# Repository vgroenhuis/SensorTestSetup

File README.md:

# SensorTestSetup

A permanent desk setup of common lab sensors and actuators around one ESP32-C5, used to explain and try out each part.
Switch it on and everything works: every part has a live page in the browser, on the university network or through the
CloSer lab demos site (https://closer.ram.eemcs.utwente.nl/labdemos/demo?id=sensortest).

| Folder | What |
| --- | --- |
| [`firmware/`](firmware/) | The firmware (ESP-IDF 6.1): every part, its web pages, the input-output matrix, updates over the air |
| [`labdemo/`](labdemo/) | The lab demos page for it (`demo.json`, `README.md`): copied to the server |
| [`ESP32_C5_Breadboard_PlatformIO/`](ESP32_C5_Breadboard_PlatformIO/) | The earlier Arduino/PlatformIO firmware, kept for reference (its README pinout is older than the wiring: `firmware/main/board.h` has the pins) |
| [`Electronics_KiCad/`](Electronics_KiCad/) | KiCad files of the setup |

The parts: SSD1306 OLED, MCP3008 (potentiometer, MH sensor), MCP23017, PCA9685 servos, TCA9548 with two WF100DPZ pressure
sensors, VL53L7CX time-of-flight, HC-SR04 ultrasonic, HX711 load cell, L298N with a DC gear motor and encoder. Build,
first flash and updates: [`firmware/README.md`](firmware/README.md).

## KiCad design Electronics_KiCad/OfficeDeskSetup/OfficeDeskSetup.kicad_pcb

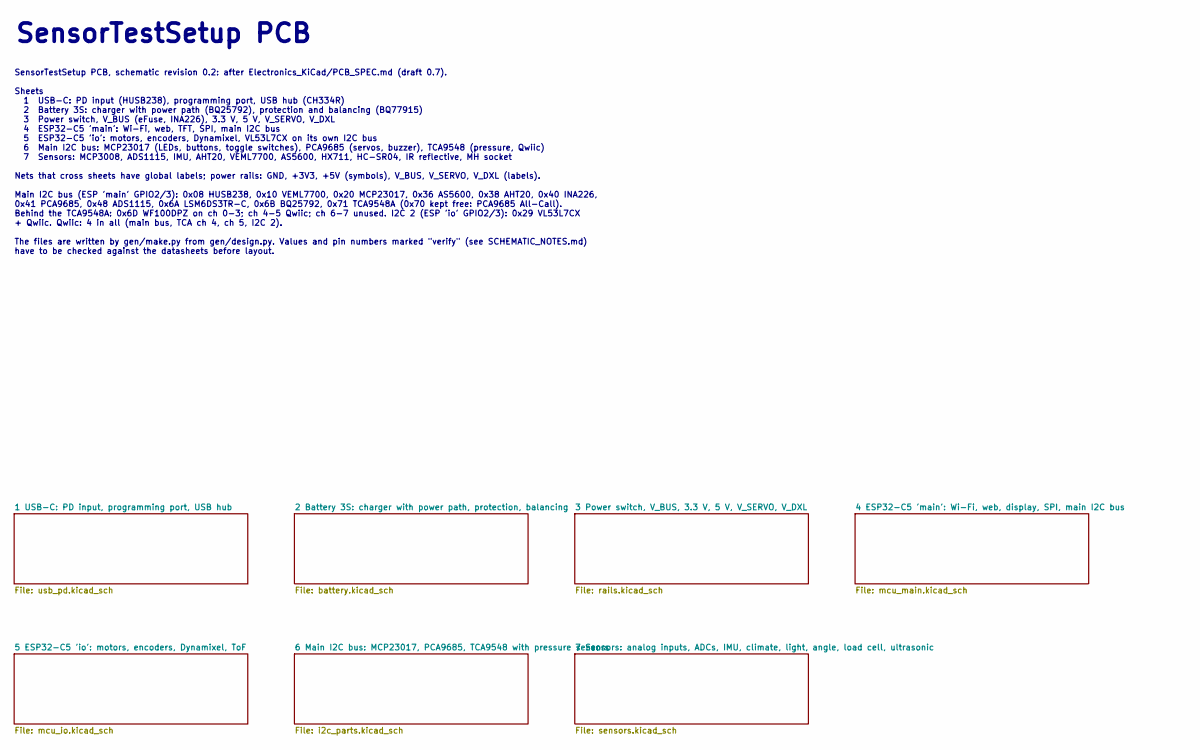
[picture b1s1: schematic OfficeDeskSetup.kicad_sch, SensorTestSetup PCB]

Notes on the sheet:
SensorTestSetup PCB
SensorTestSetup PCB, schematic revision 0.2: after Electronics_KiCad/PCB_SPEC.md (draft 0.7). Sheets 1 USB-C: PD input (HUSB238), programming port, USB hub (CH334R) 2 Battery 3S: charger with power path (BQ25792), protection and balancing (BQ77915) 3 Power switch, V_BUS (eFuse, INA226), 3.3 V, 5 V,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

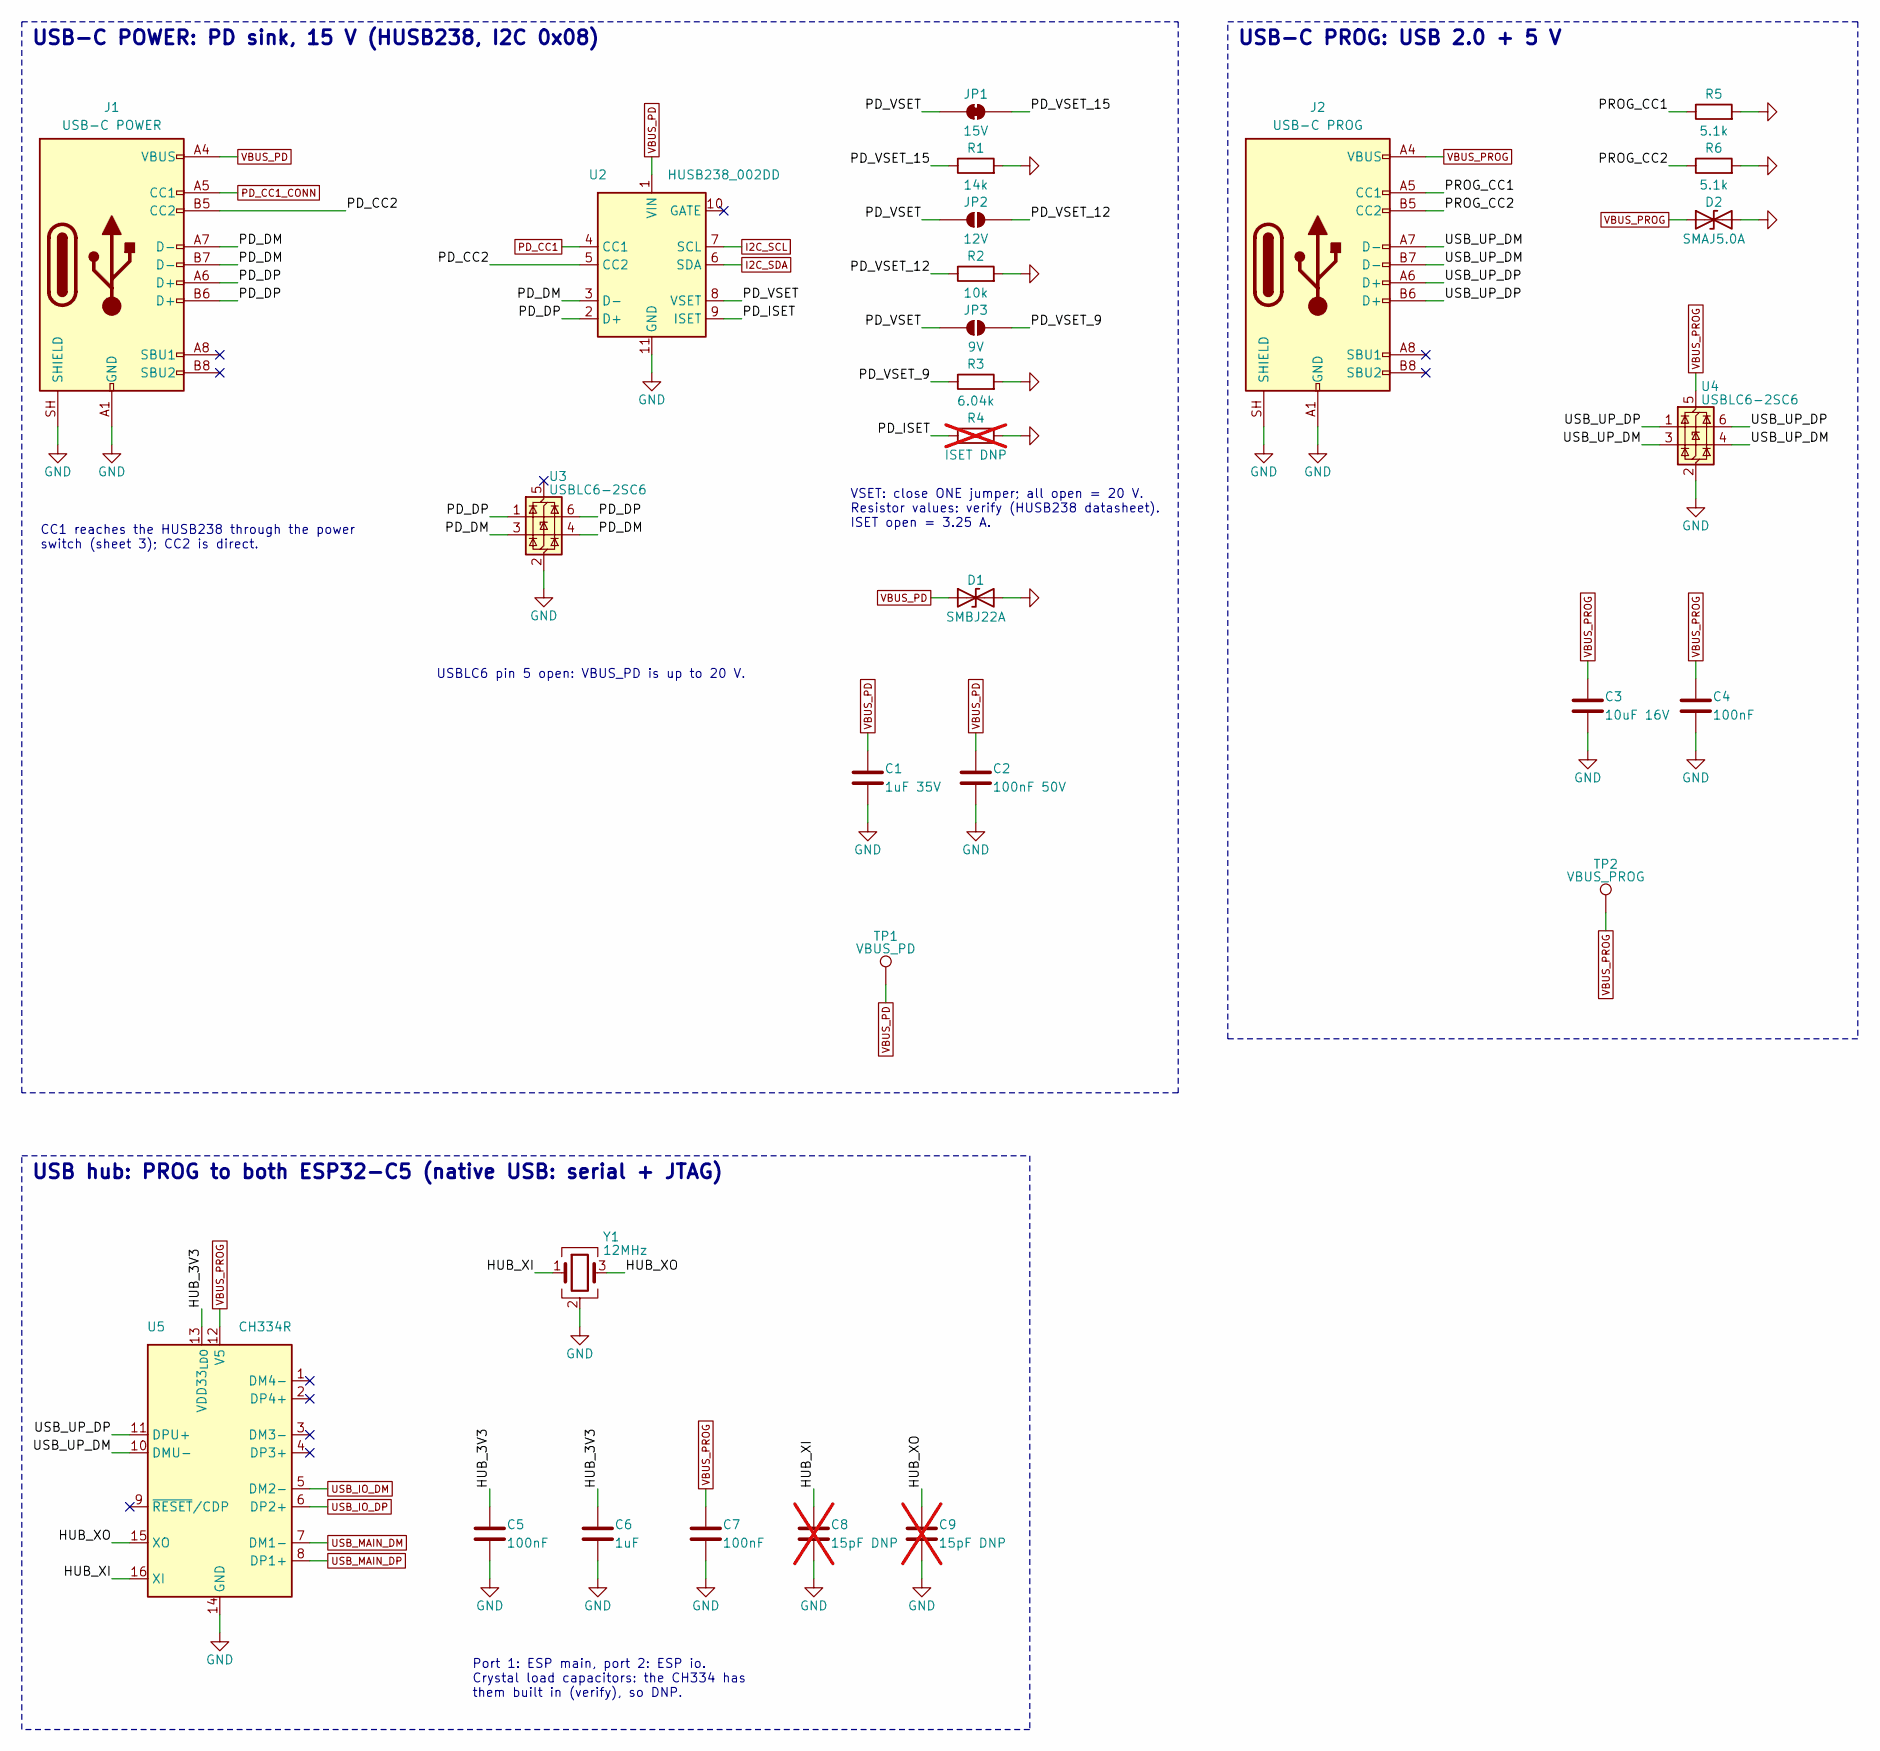
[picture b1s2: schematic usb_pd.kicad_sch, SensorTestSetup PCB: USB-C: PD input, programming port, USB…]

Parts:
C1: 1uF 35V; C_0805_2012Metric; LCSC C28323
C2: 100nF 50V; C_0603_1608Metric; LCSC C14663
C3: 10uF 16V; C_0805_2012Metric; LCSC C15850
C4, C5, C7: 100nF; C_0603_1608Metric; LCSC C14663
C6: 1uF; C_0603_1608Metric; LCSC C15849
C8, C9: 15pF DNP; C_0603_1608Metric; LCSC C1644; not fitted
D1: SMBJ22A; D_SMB; LCSC C10214
D2: SMAJ5.0A; D_SMA; LCSC C19077523
J1: USB-C POWER; USB_C_Receptacle_HRO_TYPE-C-31-M-12; LCSC C165948
J2: USB-C PROG; USB_C_Receptacle_HRO_TYPE-C-31-M-12; LCSC C165948
JP1: 15V; SolderJumper-2_P1.3mm_Bridged_RoundedPad1.0x1.5mm
JP2: 12V; SolderJumper-2_P1.3mm_Open_RoundedPad1.0x1.5mm
JP3: 9V; SolderJumper-2_P1.3mm_Open_RoundedPad1.0x1.5mm
R1: 14k; R_0603_1608Metric; LCSC C22803
R2: 10k; R_0603_1608Metric; LCSC C25804
R3: 6.04k; R_0603_1608Metric; LCSC C25977
R4: ISET DNP; R_0603_1608Metric; not fitted
R5, R6: 5.1k; R_0603_1608Metric; LCSC C23186
TP1: VBUS_PD; TestPoint_Pad_D1.5mm
TP2: VBUS_PROG; TestPoint_Pad_D1.5mm
U2: HUSB238_002DD; WDFN-10-1EP_3x3mm_P0.5mm_EP1.8x2.5mm; LCSC C7471904
U3, U4: USBLC6-2SC6; SOT-23-6; LCSC C2827654
U5: CH334R; QSOP-16_3.9x4.9mm_P0.635mm; LCSC C4154405
Y1: 12MHz; Crystal_SMD_3225-4Pin_3.2x2.5mm; LCSC C9002

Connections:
/1 USB-C: PD input, programming port, USB hub/HUB_3V3: C5.1, C6.1, U5.13 (VDD33_{LDO})
/1 USB-C: PD input, programming port, USB hub/HUB_XI: C8.1, U5.16 (XI), Y1.1
/1 USB-C: PD input, programming port, USB hub/HUB_XO: C9.1, U5.15 (XO), Y1.3
/1 USB-C: PD input, programming port, USB hub/PD_CC2: J1.B5 (CC2), U2.5 (CC2)
/1 USB-C: PD input, programming port, USB hub/PD_DM: J1.A7 (D-), J1.B7 (D-), U2.3 (D-), U3.3 (I/O2), U3.4 (I/O2)
/1 USB-C: PD input, programming port, USB hub/PD_DP: J1.A6 (D+), J1.B6 (D+), U2.2 (D+), U3.1 (I/O1), U3.6 (I/O1)
/1 USB-C: PD input, programming port, USB hub/PD_ISET: R4.1, U2.9 (ISET)
/1 USB-C: PD input, programming port, USB hub/PD_VSET: JP1.1 (A), JP2.1 (A), JP3.1 (A), U2.8 (VSET)
/1 USB-C: PD input, programming port, USB hub/PD_VSET_9: JP3.2 (B), R3.1
/1 USB-C: PD input, programming port, USB hub/PD_VSET_12: JP2.2 (B), R2.1
/1 USB-C: PD input, programming port, USB hub/PD_VSET_15: JP1.2 (B), R1.1
/1 USB-C: PD input, programming port, USB hub/PROG_CC1: J2.A5 (CC1), R5.1
/1 USB-C: PD input, programming port, USB hub/PROG_CC2: J2.B5 (CC2), R6.1
/1 USB-C: PD input, programming port, USB hub/USB_UP_DM: J2.A7 (D-), J2.B7 (D-), U4.3 (I/O2), U4.4 (I/O2), U5.10 (DMU-)
/1 USB-C: PD input, programming port, USB hub/USB_UP_DP: J2.A6 (D+), J2.B6 (D+), U4.1 (I/O1), U4.6 (I/O1), U5.11 (DPU+)
GND: C1.2, C2.2, C3.2, C4.2, C5.2, C6.2, C7.2, C8.2, C9.2, D1.2 (A2), D2.2 (A2), J1.A1 (GND), J1.A12 (GND), J1.B1 (GND), J1.B12 (GND), J1.SH (SHIELD), J2.A1 (GND), J2.A12 (GND), J2.B1 (GND), J2.B12 (GND), J2.SH (SHIELD), R1.2, R2.2, R3.2, R4.2, R5.2, R6.2, U2.11 (GND), U3.2 (GND), U4.2 (GND), U5.14 (GND), Y1.2 (G), Y1.4 (G); also elsewhere on the board
I2C_SCL: U2.7 (SCL); also elsewhere on the board
I2C_SDA: U2.6 (SDA); also elsewhere on the board
PD_CC1: U2.4 (CC1); also elsewhere on the board
PD_CC1_CONN: J1.A5 (CC1); also elsewhere on the board
USB_IO_DM: U5.5 (DM2-); also elsewhere on the board
USB_IO_DP: U5.6 (DP2+); also elsewhere on the board
USB_MAIN_DM: U5.7 (DM1-); also elsewhere on the board
USB_MAIN_DP: U5.8 (DP1+); also elsewhere on the board
VBUS_PD: C1.1, C2.1, D1.1 (A1), J1.A4 (VBUS), J1.A9 (VBUS), J1.B4 (VBUS), J1.B9 (VBUS), TP1.1, U2.1 (VIN); also elsewhere on the board
VBUS_PROG: C3.1, C4.1, C7.1, D2.1 (A1), J2.A4 (VBUS), J2.A9 (VBUS), J2.B4 (VBUS), J2.B9 (VBUS), TP2.1, U4.5 (VBUS), U5.12 (V5); also elsewhere on the board

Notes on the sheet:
CC1 reaches the HUSB238 through the power switch (sheet 3); CC2 is direct.
USBLC6 pin 5 open: VBUS_PD is up to 20 V.
VSET: close ONE jumper; all open = 20 V. Resistor values: verify (HUSB238 datasheet). ISET open = 3.25 A.
USB-C POWER: PD sink, 15 V (HUSB238, I2C 0x08)
USB-C PROG: USB 2.0 + 5 V
Port 1: ESP main, port 2: ESP io. Crystal load capacitors: the CH334 has them built in (verify), so DNP.
USB hub: PROG to both ESP32-C5 (native USB: serial + JTAG)

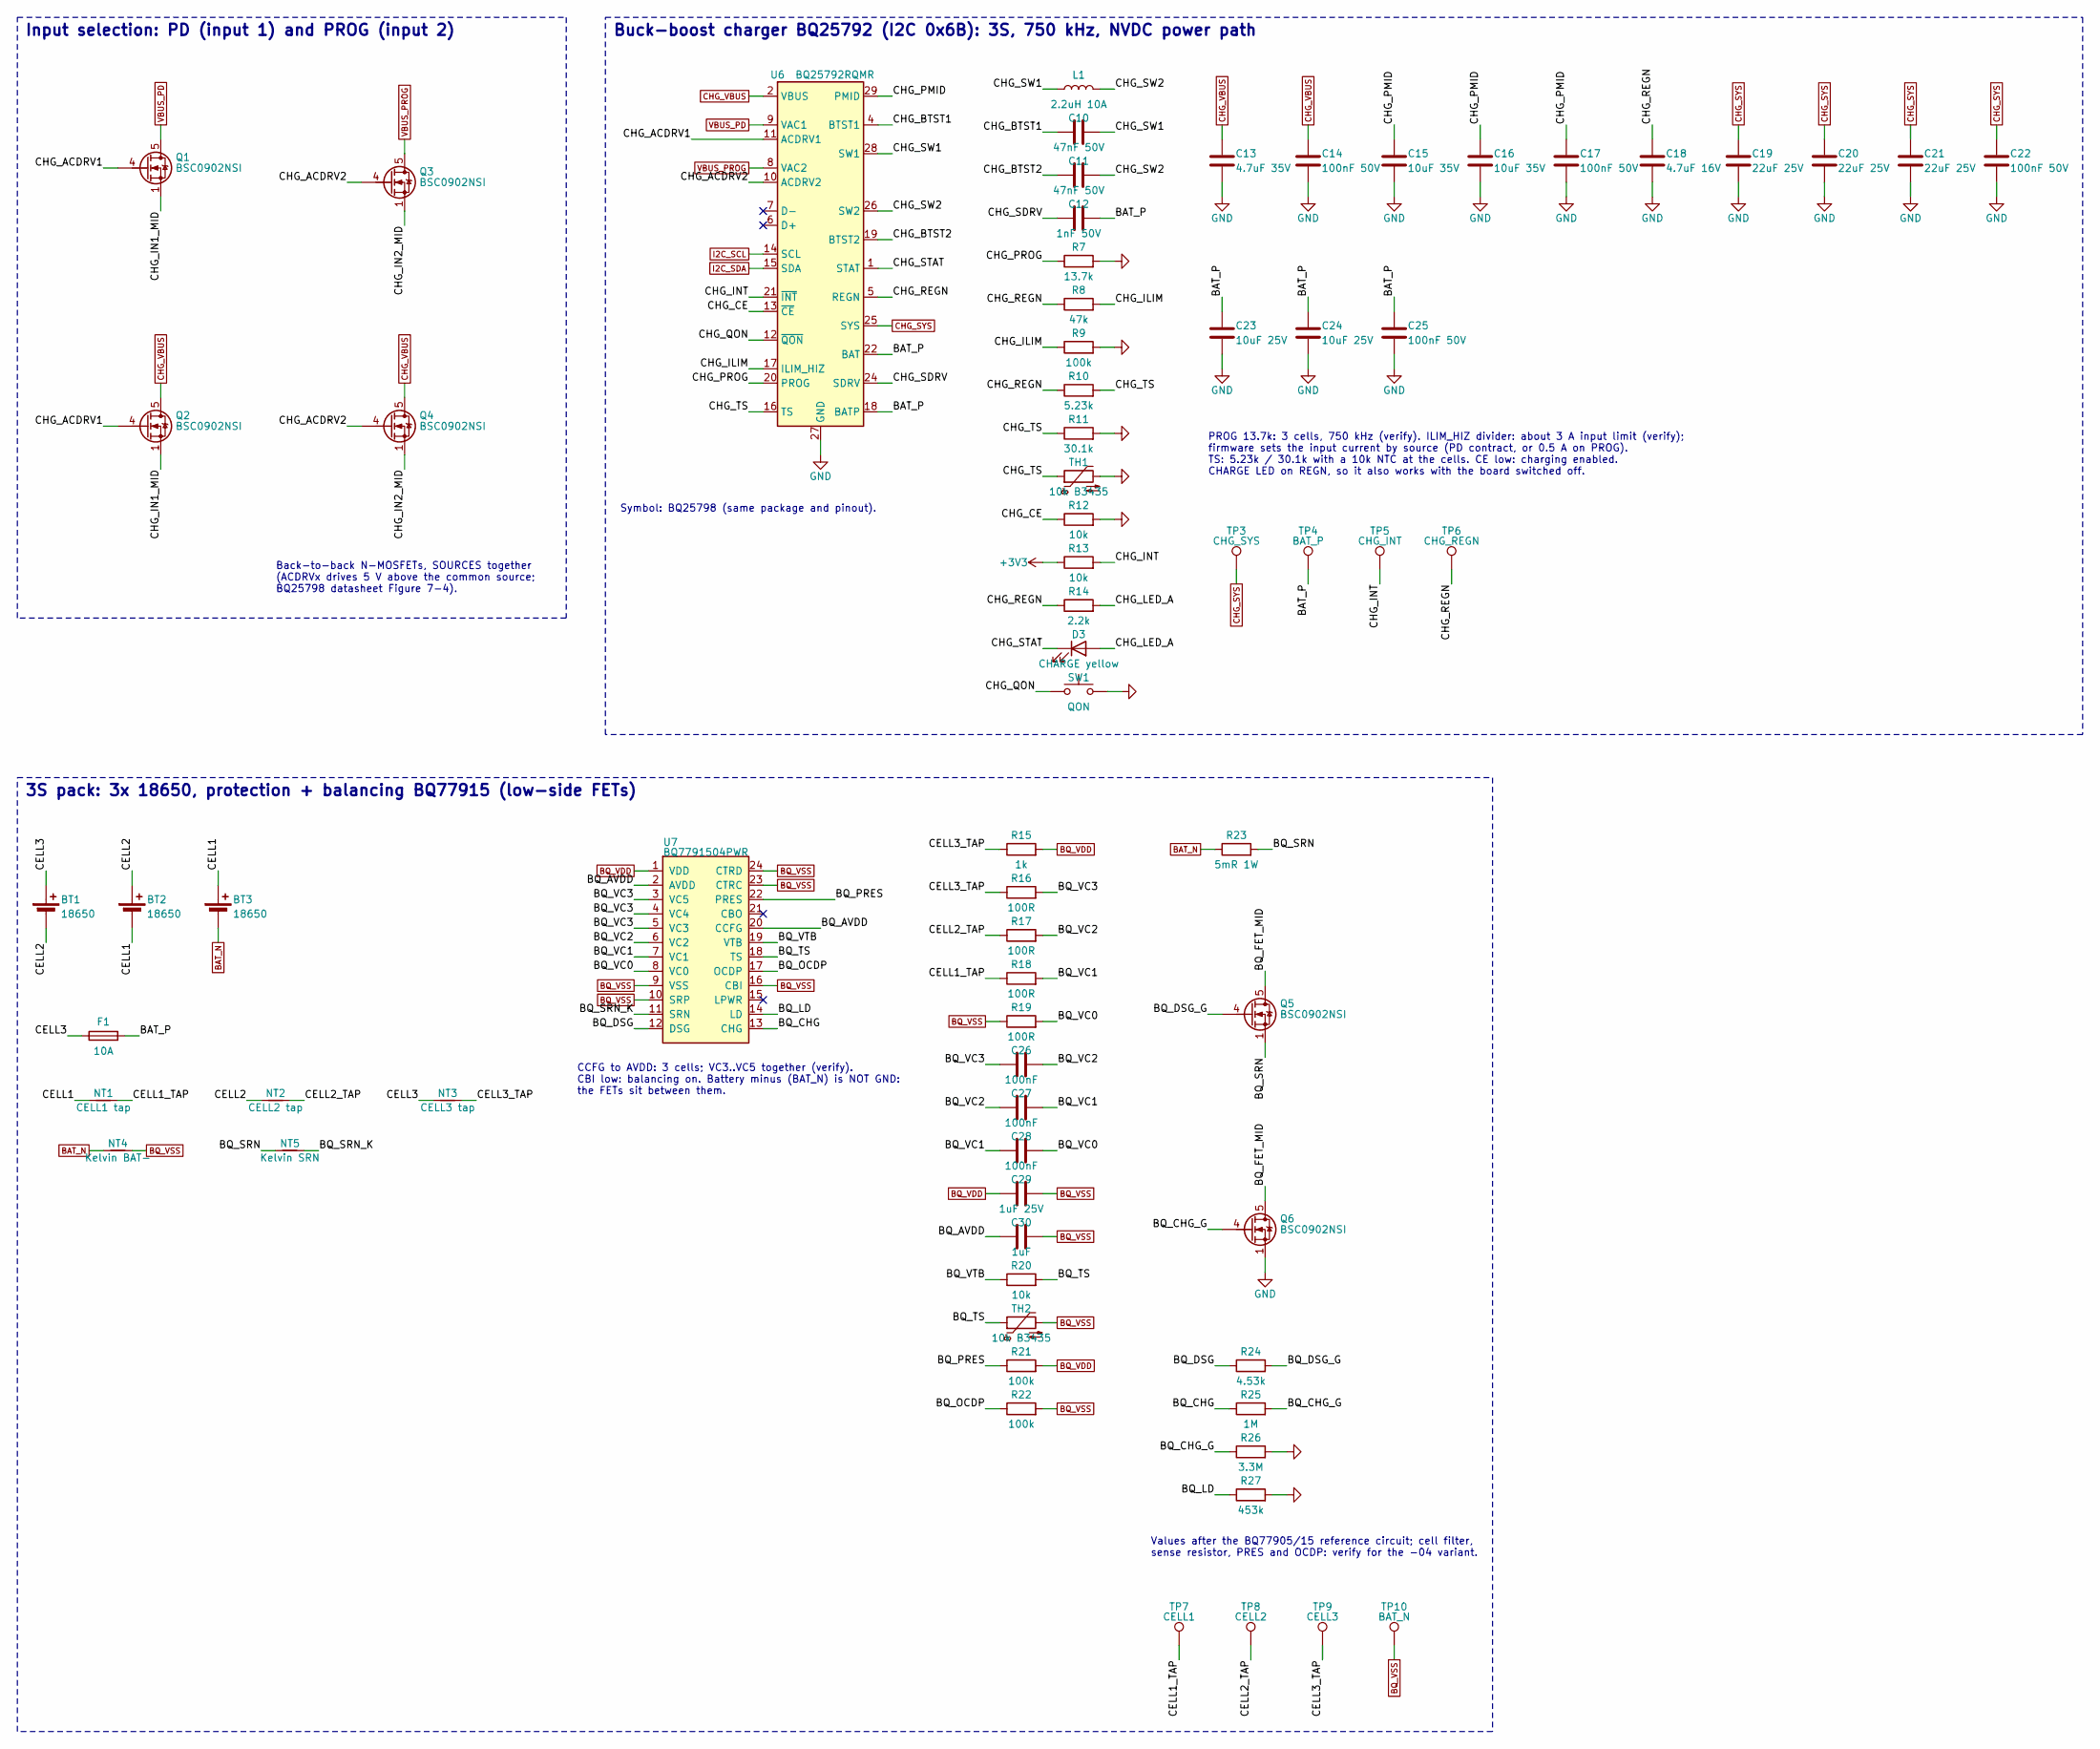
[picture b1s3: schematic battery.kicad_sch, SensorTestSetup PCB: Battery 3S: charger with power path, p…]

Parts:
BT1, BT2, BT3: 18650; BatteryHolder_Keystone_1042_1x18650; LCSC C2979183
C10, C11: 47nF 50V; C_0603_1608Metric; LCSC C1622
C12: 1nF 50V; C_0603_1608Metric; LCSC C1588
C13: 4.7uF 35V; C_0805_2012Metric; LCSC C76651
C14, C17, C22, C25: 100nF 50V; C_0603_1608Metric; LCSC C14663
C15, C16: 10uF 35V; C_1206_3216Metric; LCSC C13585
C18: 4.7uF 16V; C_0805_2012Metric; LCSC C1779
C19, C20, C21: 22uF 25V; C_1206_3216Metric; LCSC C12891
C23, C24: 10uF 25V; C_1206_3216Metric; LCSC C13585
C26, C27, C28: 100nF; C_0603_1608Metric; LCSC C14663
C29: 1uF 25V; C_0603_1608Metric; LCSC C15849
C30: 1uF; C_0603_1608Metric; LCSC C15849
D3: CHARGE yellow; LED_0603_1608Metric; LCSC C2287
F1: 10A; Fuse_Littelfuse-NANO2-451_453; LCSC C44479
L1: 2.2uH 10A; IND-SMD_L11.5-W10.5; LCSC C167228
NT1: CELL1 tap; NetTie-2_SMD_Pad0.5mm
NT2: CELL2 tap; NetTie-2_SMD_Pad0.5mm
NT3: CELL3 tap; NetTie-2_SMD_Pad0.5mm
NT4: Kelvin BAT-; NetTie-2_SMD_Pad0.5mm
NT5: Kelvin SRN; NetTie-2_SMD_Pad0.5mm
Q1, Q2, Q3, Q4, Q5, Q6: BSC0902NSI; TDSON-8-1; LCSC C534382
R7: 13.7k; R_0603_1608Metric; LCSC C22793
R8: 47k; R_0603_1608Metric; LCSC C25819
R9, R21, R22: 100k; R_0603_1608Metric; LCSC C25803
R10: 5.23k; R_0603_1608Metric; LCSC C23068
R11: 30.1k; R_0603_1608Metric; LCSC C23000
R12, R13, R20: 10k; R_0603_1608Metric; LCSC C25804
R14: 2.2k; R_0603_1608Metric; LCSC C4190
R15: 1k; R_0603_1608Metric; LCSC C21190
R16, R17, R18, R19: 100R; R_0603_1608Metric; LCSC C22775
R23: 5mR 1W; R_2512_6332Metric; LCSC C393074
R24: 4.53k; R_0603_1608Metric; LCSC C25971
R25: 1M; R_0603_1608Metric; LCSC C22935
R26: 3.3M; R_0603_1608Metric; LCSC C26096
R27: 453k; R_0603_1608Metric; LCSC C25818
SW1: QON; SW-SMD_4P-L5.1-W5.1-P3.70-LS6.5-TL_H1.5; LCSC C318884
TH1, TH2: 10k B3435; R_0603_1608Metric; LCSC C525660
TP3: CHG_SYS; TestPoint_Pad_D1.5mm
TP4: BAT_P; TestPoint_Pad_D1.5mm
TP5: CHG_INT; TestPoint_Pad_D1.5mm
TP6: CHG_REGN; TestPoint_Pad_D1.5mm
TP7: CELL1; TestPoint_Pad_D1.5mm
TP8: CELL2; TestPoint_Pad_D1.5mm
TP9: CELL3; TestPoint_Pad_D1.5mm
TP10: BAT_N; TestPoint_Pad_D1.5mm
U6: BQ25792RQMR; Texas_RQM0029A_VQFN-29_4x4mm_P0.4mm; LCSC C2862876
U7: BQ7791504PWR; TSSOP-24_4.4x7.8mm_P0.65mm; LCSC C2873309

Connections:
+3V3: R13.1; also elsewhere on the board
/2 Battery 3S: charger with power path, protection, balancing/BAT_P: C12.2, C23.1, C24.1, C25.1, F1.2, TP4.1, U6.18 (BATP), U6.22 (BAT), U6.23 (BAT)
/2 Battery 3S: charger with power path, protection, balancing/BQ_AVDD: C30.1, U7.2 (AVDD), U7.20 (CCFG)
/2 Battery 3S: charger with power path, protection, balancing/BQ_CHG: R25.1, U7.13 (CHG)
/2 Battery 3S: charger with power path, protection, balancing/BQ_CHG_G: Q6.4 (G), R25.2, R26.1
/2 Battery 3S: charger with power path, protection, balancing/BQ_DSG: R24.1, U7.12 (DSG)
/2 Battery 3S: charger with power path, protection, balancing/BQ_DSG_G: Q5.4 (G), R24.2
/2 Battery 3S: charger with power path, protection, balancing/BQ_FET_MID: Q5.5 (D), Q6.5 (D)
/2 Battery 3S: charger with power path, protection, balancing/BQ_LD: R27.1, U7.14 (LD)
/2 Battery 3S: charger with power path, protection, balancing/BQ_OCDP: R22.1, U7.17 (OCDP)
/2 Battery 3S: charger with power path, protection, balancing/BQ_PRES: R21.1, U7.22 (PRES)
/2 Battery 3S: charger with power path, protection, balancing/BQ_SRN: NT5.1, Q5.1 (S), Q5.2 (S), Q5.3 (S), R23.2
/2 Battery 3S: charger with power path, protection, balancing/BQ_SRN_K: NT5.2, U7.11 (SRN)
/2 Battery 3S: charger with power path, protection, balancing/BQ_TS: R20.2, TH2.1, U7.18 (TS)
/2 Battery 3S: charger with power path, protection, balancing/BQ_VC0: C28.2, R19.2, U7.8 (VC0)
/2 Battery 3S: charger with power path, protection, balancing/BQ_VC1: C27.2, C28.1, R18.2, U7.7 (VC1)
/2 Battery 3S: charger with power path, protection, balancing/BQ_VC2: C26.2, C27.1, R17.2, U7.6 (VC2)
/2 Battery 3S: charger with power path, protection, balancing/BQ_VC3: C26.1, R16.2, U7.3 (VC5), U7.4 (VC4), U7.5 (VC3)
/2 Battery 3S: charger with power path, protection, balancing/BQ_VTB: R20.1, U7.19 (VTB)
/2 Battery 3S: charger with power path, protection, balancing/CELL1: BT2.2 (-), BT3.1 (+), NT1.1
/2 Battery 3S: charger with power path, protection, balancing/CELL1_TAP: NT1.2, R18.1, TP7.1
/2 Battery 3S: charger with power path, protection, balancing/CELL2: BT1.2 (-), BT2.1 (+), NT2.1
/2 Battery 3S: charger with power path, protection, balancing/CELL2_TAP: NT2.2, R17.1, TP8.1
/2 Battery 3S: charger with power path, protection, balancing/CELL3: BT1.1 (+), F1.1, NT3.1
/2 Battery 3S: charger with power path, protection, balancing/CELL3_TAP: NT3.2, R15.1, R16.1, TP9.1
/2 Battery 3S: charger with power path, protection, balancing/CHG_ACDRV1: Q1.4 (G), Q2.4 (G), U6.11 (ACDRV1)
/2 Battery 3S: charger with power path, protection, balancing/CHG_ACDRV2: Q3.4 (G), Q4.4 (G), U6.10 (ACDRV2)
/2 Battery 3S: charger with power path, protection, balancing/CHG_BTST1: C10.1, U6.4 (BTST1)
/2 Battery 3S: charger with power path, protection, balancing/CHG_BTST2: C11.1, U6.19 (BTST2)
/2 Battery 3S: charger with power path, protection, balancing/CHG_CE: R12.1, U6.13 (~CE)
/2 Battery 3S: charger with power path, protection, balancing/CHG_ILIM: R8.2, R9.1, U6.17 (ILIM_HIZ)
/2 Battery 3S: charger with power path, protection, balancing/CHG_IN1_MID: Q1.1 (S), Q1.2 (S), Q1.3 (S), Q2.1 (S), Q2.2 (S), Q2.3 (S)
/2 Battery 3S: charger with power path, protection, balancing/CHG_IN2_MID: Q3.1 (S), Q3.2 (S), Q3.3 (S), Q4.1 (S), Q4.2 (S), Q4.3 (S)
/2 Battery 3S: charger with power path, protection, balancing/CHG_INT: R13.2, TP5.1, U6.21 (~INT)
/2 Battery 3S: charger with power path, protection, balancing/CHG_LED_A: D3.2 (A), R14.2
/2 Battery 3S: charger with power path, protection, balancing/CHG_PMID: C15.1, C16.1, C17.1, U6.29 (PMID)
/2 Battery 3S: charger with power path, protection, balancing/CHG_PROG: R7.1, U6.20 (PROG)
/2 Battery 3S: charger with power path, protection, balancing/CHG_QON: SW1.1, U6.12 (~QON)
/2 Battery 3S: charger with power path, protection, balancing/CHG_REGN: C18.1, R8.1, R10.1, R14.1, TP6.1, U6.5 (REGN)
/2 Battery 3S: charger with power path, protection, balancing/CHG_SDRV: C12.1, U6.24 (SDRV)
/2 Battery 3S: charger with power path, protection, balancing/CHG_STAT: D3.1 (K), U6.1 (STAT)
/2 Battery 3S: charger with power path, protection, balancing/CHG_SW1: C10.2, L1.1, U6.28 (SW1)
/2 Battery 3S: charger with power path, protection, balancing/CHG_SW2: C11.2, L1.2, U6.26 (SW2)
/2 Battery 3S: charger with power path, protection, balancing/CHG_TS: R10.2, R11.1, TH1.1, U6.16 (TS)
BAT_N: BT3.2 (-), NT4.1, R23.1
BQ_VDD: C29.1, R15.2, R21.2, U7.1 (VDD)
BQ_VSS: C29.2, C30.2, NT4.2, R19.1, R22.2, TH2.2, TP10.1, U7.9 (VSS), U7.10 (SRP), U7.16 (CBI), U7.23 (CTRC), U7.24 (CTRD)
CHG_SYS: C19.1, C20.1, C21.1, C22.1, TP3.1, U6.25 (SYS); also elsewhere on the board
CHG_VBUS: C13.1, C14.1, Q2.5 (D), Q4.5 (D), U6.2 (VBUS), U6.3 (VBUS)
GND: C13.2, C14.2, C15.2, C16.2, C17.2, C18.2, C19.2, C20.2, C21.2, C22.2, C23.2, C24.2, C25.2, Q6.1 (S), Q6.2 (S), Q6.3 (S), R7.2, R9.2, R11.2, R12.2, R26.2, R27.2, SW1.2, TH1.2, U6.27 (GND); also elsewhere on the board
I2C_SCL: U6.14 (SCL); also elsewhere on the board
I2C_SDA: U6.15 (SDA); also elsewhere on the board
VBUS_PD: Q1.5 (D), U6.9 (VAC1); also elsewhere on the board
VBUS_PROG: Q3.5 (D), U6.8 (VAC2); also elsewhere on the board

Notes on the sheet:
Back-to-back N-MOSFETs, SOURCES together (ACDRVx drives 5 V above the common source; BQ25798 datasheet Figure 7-4).
Input selection: PD (input 1) and PROG (input 2)
Symbol: BQ25798 (same package and pinout).
PROG 13.7k: 3 cells, 750 kHz (verify). ILIM_HIZ divider: about 3 A input limit (verify); firmware sets the input current by source (PD contract, or 0.5 A on PROG). TS: 5.23k / 30.1k with a 10k NTC at the cells. CE low: charging enabled. CHARGE LED on REGN, so it also works with the board switched o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
Buck-boost charger BQ25792 (I2C 0x6B): 3S, 750 kHz, NVDC power path
CCFG to AVDD: 3 cells; VC3..VC5 together (verify). CBI low: balancing on. Battery minus (BAT_N) is NOT GND: the FETs sit between them.
Values after the BQ77905/15 reference circuit; cell filter, sense resistor, PRES and OCDP: verify for the -04 variant.
3S pack: 3x 18650, protection + balancing BQ77915 (low-side FETs)
